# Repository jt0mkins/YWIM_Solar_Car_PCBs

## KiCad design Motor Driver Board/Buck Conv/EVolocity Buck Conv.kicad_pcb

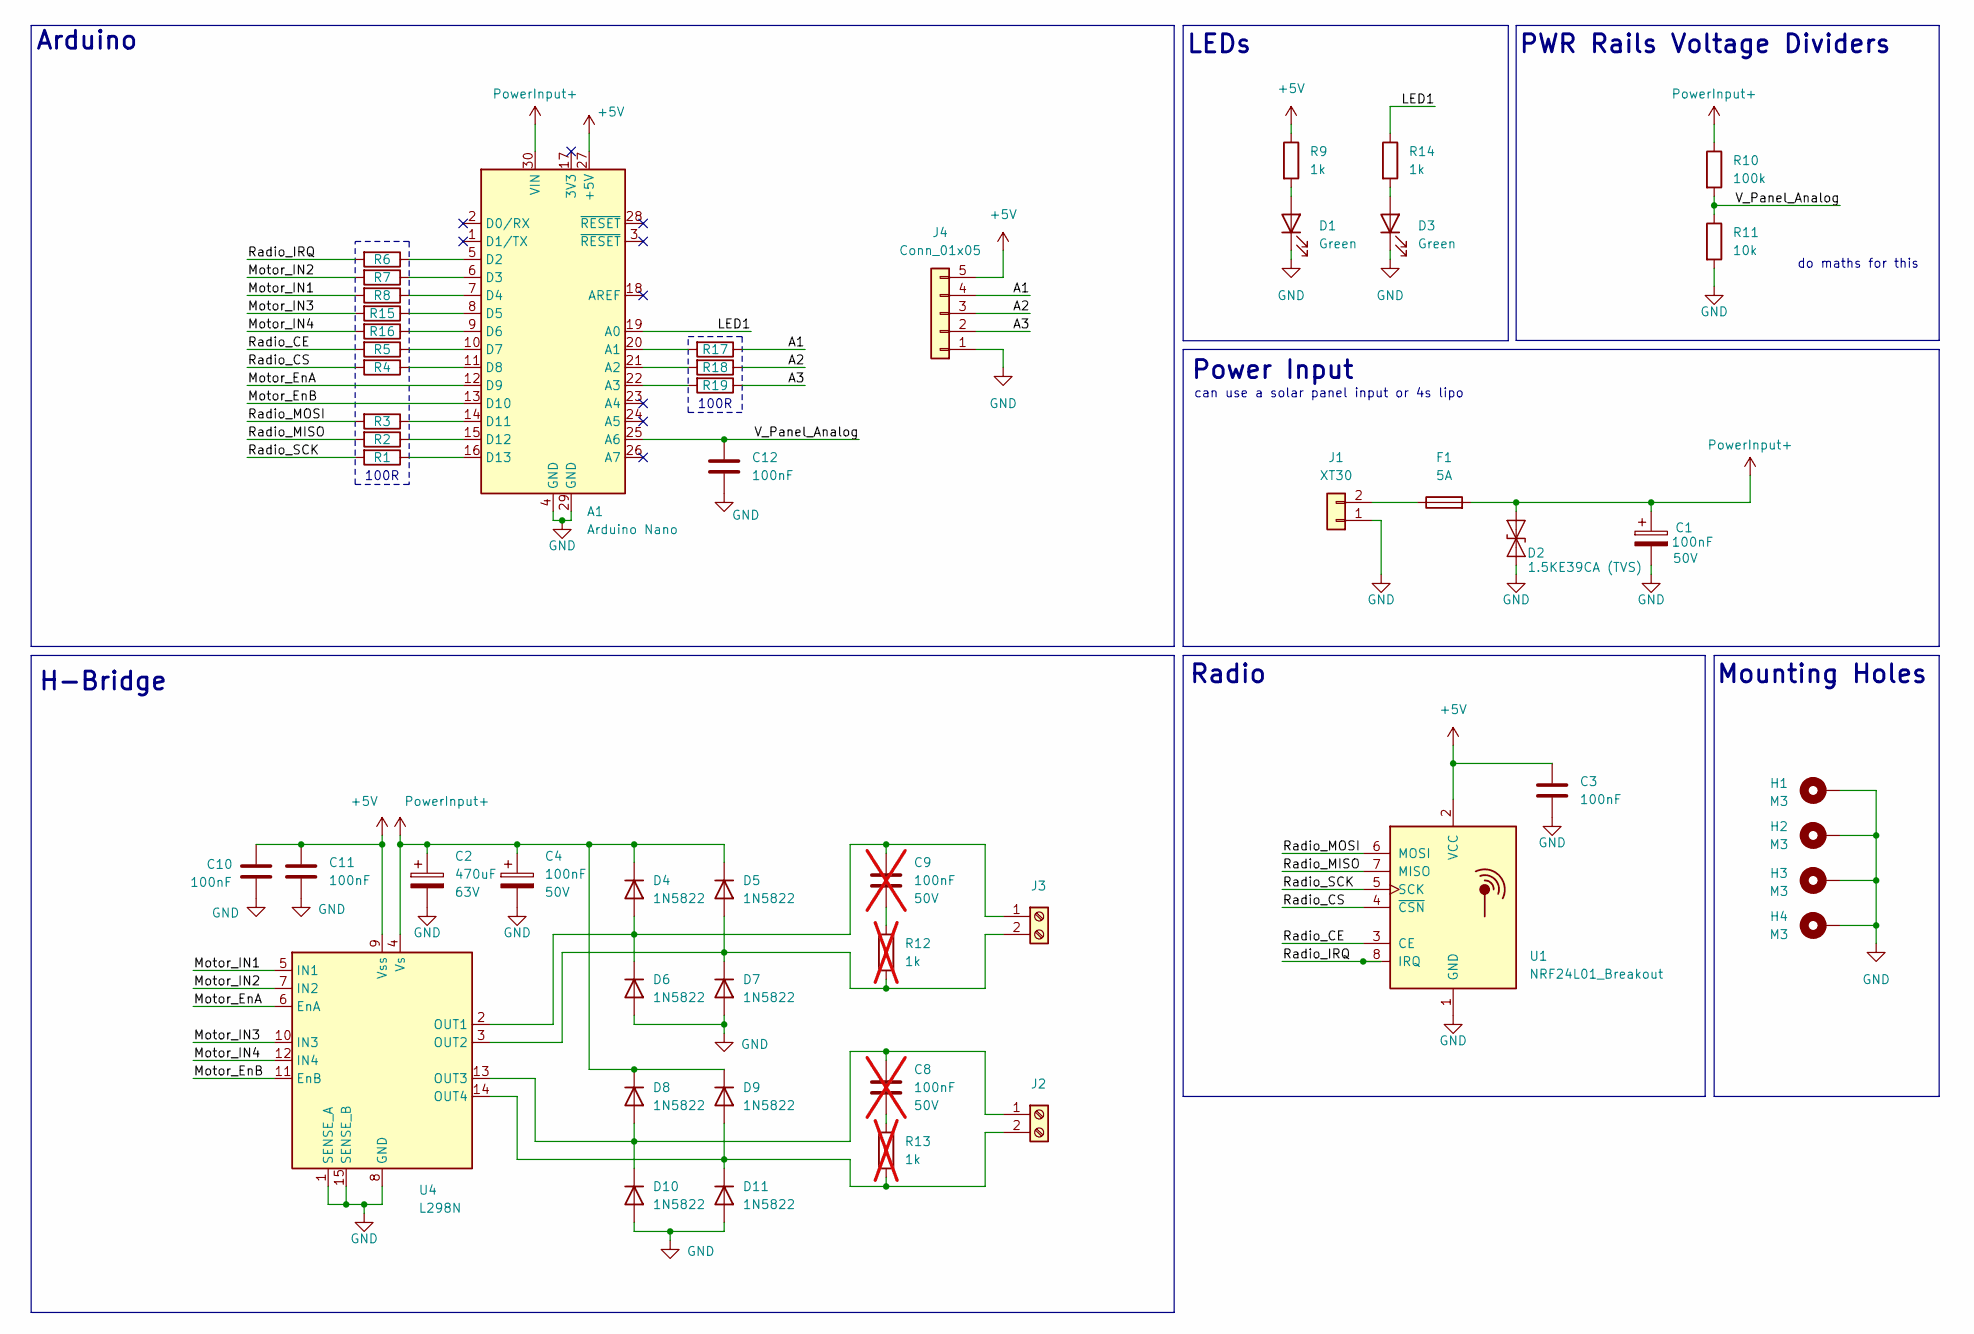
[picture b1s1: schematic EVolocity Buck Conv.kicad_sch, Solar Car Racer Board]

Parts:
A1: Arduino Nano; Arduino_Nano; Voltage 50V; MPN SR205C104KAR; LCSC Part No. C1620866
C1, C3, C4, C10, C11, C12: 100nF; C_Rect_L7.0mm_W2.5mm_P5.00mm; Voltage 50V; MPN SR205C104KAR; LCSC Part No. C1620866
C2: 470uF; CP_Radial_D12.5mm_P5.00mm; Voltage 63V
C8, C9: 100nF; C_Rect_L7.0mm_W2.5mm_P5.00mm; Voltage 50V; MPN SR205C104KAR; LCSC Part No. C1620866; not fitted
D1, D3: Green; LED_D3.0mm_FlatTop; MPN TLHG4400; LCSC Part No. C3001646
D2: 1.5KE39CA (TVS); D_DO-201_P12.70mm_Horizontal; LCSC Part No. C3034419
D4, D5, D6, D7, D8, D9, D10, D11: 1N5822; D_DO-201AD_P15.24mm_Horizontal; MPN 1N5822; LCSC Part No. C2476
F1: 5A; R_Axial_DIN0204_L3.6mm_D1.6mm_P5.08mm_Horizontal; MPN 2010T5A250V; LCSC Part No. C354906
H1, H2, H3, H4: M3; MountingHole_3.2mm_M3_DIN965_Pad
J1: XT30; AMASS_XT30U-F_1x02_P5.0mm_Vertical; MPN XT30U-F; LCSC Part No. C99102
J2, J3: Screw_Terminal_01x02; TerminalBlock_MaiXu_MX126-5.0-02P_1x02_P5.00mm; MPN 1935161; LCSC Part No. C3819953
J4: Conn_01x05; PinHeader_1x05_P2.54mm_Vertical
R1, R2, R3, R4, R5, R6, R7, R8, R15, R16, R17, R18, R19: 100R; R_Axial_DIN0207_L6.3mm_D2.5mm_P10.16mm_Horizontal; MPN MF0207FRE52-100R; LCSC Part No. C3508583
R9, R14: 1k; R_Axial_DIN0207_L6.3mm_D2.5mm_P10.16mm_Horizontal; MPN MF0207FTE52-1K; LCSC Part No. C513706
R10: 100k; R_Axial_DIN0207_L6.3mm_D2.5mm_P10.16mm_Horizontal; MPN MF0207FTE52-100K; LCSC Part No. C513592
R11: 10k; R_Axial_DIN0207_L6.3mm_D2.5mm_P10.16mm_Horizontal; MPN MF0207FTE52-10K; LCSC Part No. C513672
R12, R13: 1k; R_Axial_DIN0411_L9.9mm_D3.6mm_P12.70mm_Horizontal; MPN RN1WS1KΩFT/BA1; LCSC Part No. C385291; not fitted
U1: NRF24L01_Breakout; nRF24L01_Breakout
U4: L298N; TO-220-15_P2.54x5.08mm_StaggerOdd_Lead4.58mm_Vertical; LCSC Part No. C434589

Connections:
+5V: A1.27 (+5V), C3.1, C10.1, C11.1, J4.5, R9.1, U1.2 (VCC), U4.9 (Vss)
/A1: J4.4, R17.1
/A2: J4.3, R18.1
/A3: J4.2, R19.1
/LED1: A1.19 (A0), R14.1
/Motor_EnA: A1.12 (D9), U4.6 (EnA)
/Motor_EnB: A1.13 (D10), U4.11 (EnB)
/Motor_IN1: R8.2, U4.5 (IN1)
/Motor_IN2: R7.2, U4.7 (IN2)
/Motor_IN3: R15.2, U4.10 (IN3)
/Motor_IN4: R16.2, U4.12 (IN4)
/Radio_CE: R5.2, U1.3 (CE)
/Radio_CS: R4.2, U1.4 (~CSN)
/Radio_IRQ: R6.2, U1.8 (IRQ)
/Radio_MISO: R2.2, U1.7 (MISO)
/Radio_MOSI: R3.2, U1.6 (MOSI)
/Radio_SCK: R1.2, U1.5 (SCK)
/V_Panel_Analog: A1.25 (A6), C12.1, R10.2, R11.1
GND: A1.4 (GND), A1.29 (GND), C1.2, C2.2, C3.2, C4.2, C10.2, C11.2, C12.2, D1.1 (K), D2.2 (A2), D3.1 (K), D6.2 (A), D7.2 (A), D10.2 (A), D11.2 (A), H1.1 (1_1), H2.1 (1_1), H3.1 (1_1), H4.1 (1_1), J1.1, J4.1, R11.2, U1.1 (GND), U4.1 (SENSE_A), U4.8 (GND), U4.15 (SENSE_B)
unnamed: A1.20 (A1), R17.2
unnamed: A1.21 (A2), R18.2
unnamed: A1.22 (A3), R19.2
unnamed: A1.5 (D2), R6.1
unnamed: A1.6 (D3), R7.1
unnamed: A1.7 (D4), R8.1
unnamed: A1.8 (D5), R15.1
unnamed: A1.9 (D6), R16.1
unnamed: A1.10 (D7), R5.1
unnamed: A1.11 (D8), R4.1
unnamed: A1.14 (D11), R3.1
unnamed: A1.15 (D12), R2.1
unnamed: A1.16 (D13), R1.1
unnamed: C8.2, R13.1
unnamed: C9.2, R12.1
unnamed: D1.2 (A), R9.2
unnamed: D3.2 (A), R14.2
unnamed: C9.1, D4.2 (A), D6.1 (K), J3.1, U4.2 (OUT1)
unnamed: D5.2 (A), D7.1 (K), J3.2, R12.2, U4.3 (OUT2)
unnamed: C8.1, D8.2 (A), D10.1 (K), J2.1, U4.13 (OUT3)
unnamed: D9.2 (A), D11.1 (K), J2.2, R13.2, U4.14 (OUT4)
unnamed: F1.1, J1.2
PowerInput+: A1.30 (VIN), C1.1, C2.1, C4.1, D2.1 (A1), D4.1 (K), D5.1 (K), D8.1 (K), D9.1 (K), F1.2, R10.1, U4.4 (Vs)

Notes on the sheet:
can use a solar panel input or 4s lipo
H-Bridge
100R
Radio
do maths for this
Arduino
Power Input
LEDs
Mounting Holes
PWR Rails Voltage Dividers

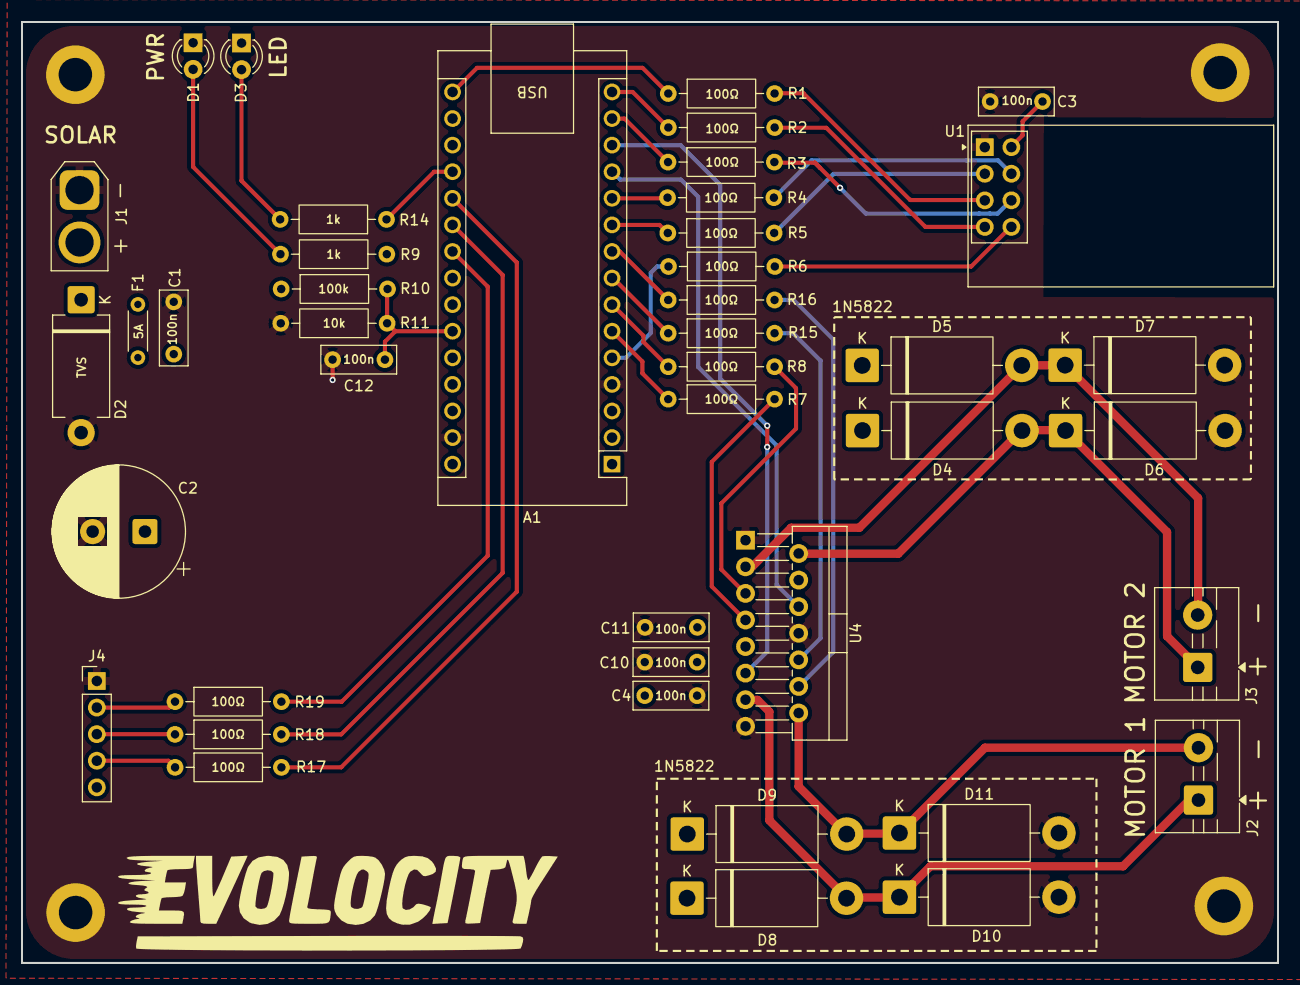
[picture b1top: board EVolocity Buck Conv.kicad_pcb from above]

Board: 4 copper layers, 120.0 x 89.9 mm, 47 parts (0 on the bottom side), 40 nets.
